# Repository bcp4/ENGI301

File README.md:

<h1>ENGI301</h1>
Repository for ENGI301

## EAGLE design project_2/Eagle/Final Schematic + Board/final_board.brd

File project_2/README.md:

This project involved creating a schematic as well as a printed circuit board for an etch a sketch. Students were tasked with importing an SPI screen in addition
to utilizing the libraries from class. Students were then able to submit their boards to macrofab.com and get an estimate for what it might cost to produce 
these PCB boards in bulk. As a result, students were able to gain a better understanding of how to create schematics and wire PCBs, as well as the process of 
documenting such a project for manufacturing and documentation reasons. 
What to expect in project_2
  -final schematic + board for the etch-a-sketch device
  -manufacturing documents (gerber files + assembly + drill files)
  -documentation (photos of top and bottom of board + mechanical drawing) 
  -bill of materials 
  -PDF of final schematic

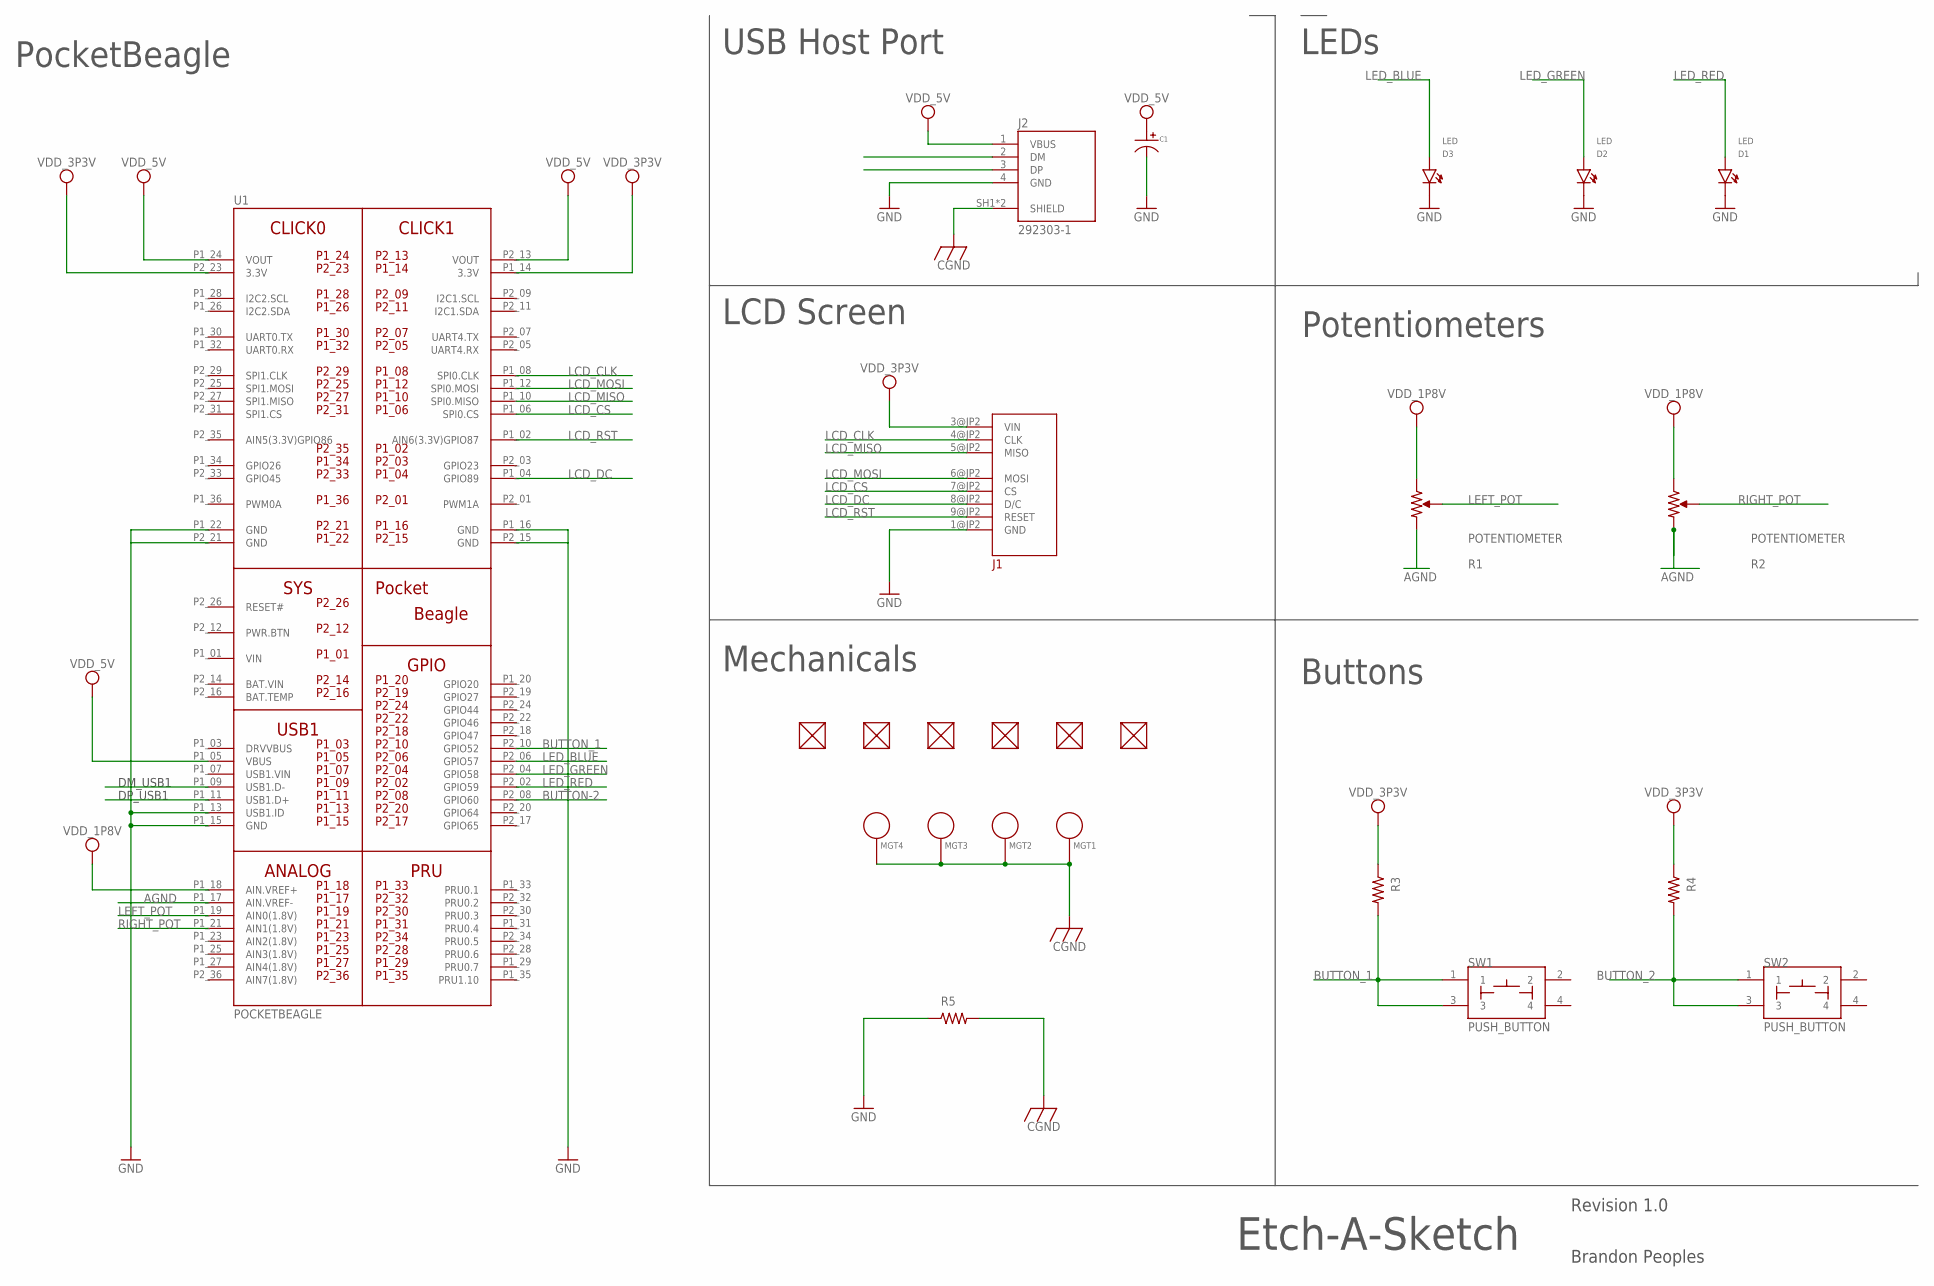
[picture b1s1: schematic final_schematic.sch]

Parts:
C1: CAPACITOR_P_10MM; CP10MM
D1, D2, D3: LED; EIA-STD
FUD1, FUD2, FUD4, FUD5, FUD6, FUD7: FIDUCIAL; FIDUCIAL_40MIL
J1: LCD; TFT_LCD_PCB
J2: 292303-1; TE_292303-1
MGT1, MGT2, MGT3, MGT4: MOUNTING_HOLE
R1, R2: POTENTIOMETER; POT-PO90S
R3, R4, R5: R_R0402; R0402
SW1, SW2: PUSH_BUTTON; BUTTON_12.5MM
U1: POCKETBEAGLE

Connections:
AGND: R1.CW, R2.CW, U1.P1_17 (AIN.VREF-)
BAT.VIN: U1.P2_14 (BAT.VIN)
BUTTON-2: U1.P2_08 (GPIO60)
BUTTON_1: R3.2, SW1.1, SW1.3, U1.P2_10 (GPIO52)
BUTTON_2: R4.2, SW2.1, SW2.3
CGND: J2.SH1 (SHIELD), J2.SH2 (SHIELD), MGT1.P$1, MGT2.P$1, MGT3.P$1, MGT4.P$1, R5.2
GND: C1.P$2, D1.CATHODE, D2.CATHODE, D3.CATHODE, J1.1@JP2 (GND), J2.4 (GND), R5.1, U1.P1_13 (USB1.ID), U1.P1_15 (GND), U1.P1_16 (GND), U1.P1_22 (GND), U1.P2_15 (GND), U1.P2_21 (GND)
LCD_CLK: J1.4@JP2 (CLK), U1.P1_08 (SPI0.CLK)
LCD_CS: J1.7@JP2 (CS), U1.P1_06 (SPI0.CS)
LCD_DC: J1.8@JP2 (D/C), U1.P1_04 (GPIO89)
LCD_MISO: J1.5@JP2 (MISO), U1.P1_10 (SPI0.MISO)
LCD_MOSI: J1.6@JP2 (MOSI), U1.P1_12 (SPI0.MOSI)
LCD_RST: J1.9@JP2 (RESET), U1.P1_02 (AIN6(3.3V)GPIO87)
LED_BLUE: D3.ANODE, U1.P2_06 (GPIO57)
LED_GREEN: D2.ANODE, U1.P2_04 (GPIO58)
LED_RED: D1.ANODE, U1.P2_02 (GPIO59)
LEFT_POT: R1.S, U1.P1_19 (AIN0(1.8V))
RIGHT_POT: R2.S, U1.P1_21 (AIN1(1.8V))
VDD_1P8V: R1.CCW, R2.CCW, U1.P1_18 (AIN.VREF+)
VDD_3P3V: J1.3@JP2 (VIN), R3.1, R4.1, U1.P1_14 (3.3V), U1.P2_23 (3.3V)
VDD_5V: C1.P$1, J2.1 (VBUS), U1.P1_05 (VBUS), U1.P1_24 (VOUT), U1.P2_13 (VOUT)
VIN: U1.P1_01 (VIN)

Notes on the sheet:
LEDs
Potentiometers
Buttons
USB Host Port
Etch-A-Sketch
LCD Screen
DM_USB1
DP_USB1
PocketBeagle
Mechanicals
Brandon Peoples
Revision 1.0

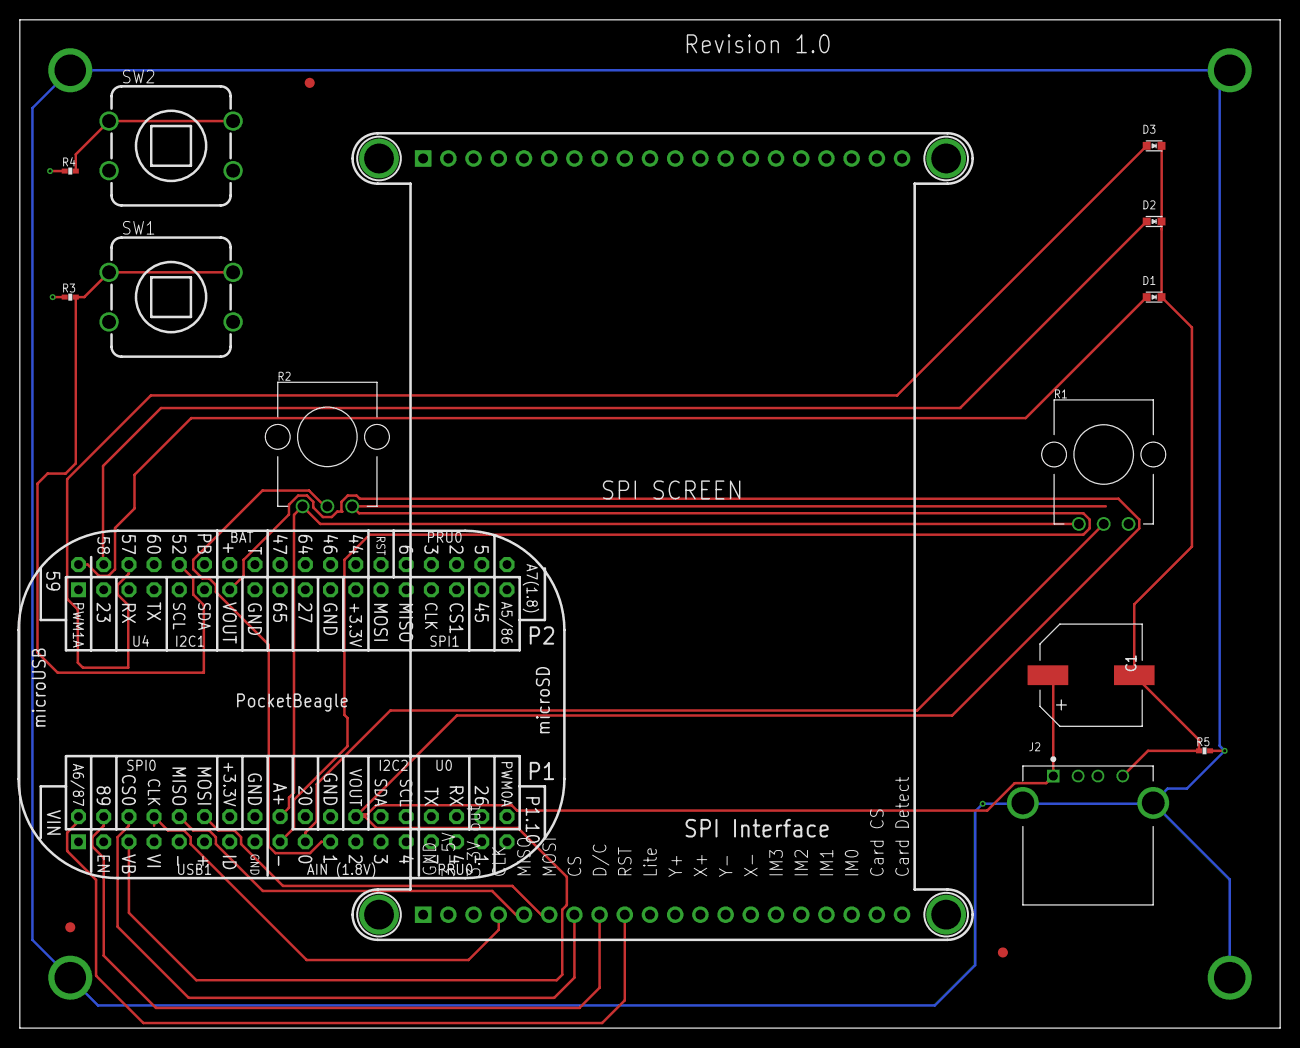
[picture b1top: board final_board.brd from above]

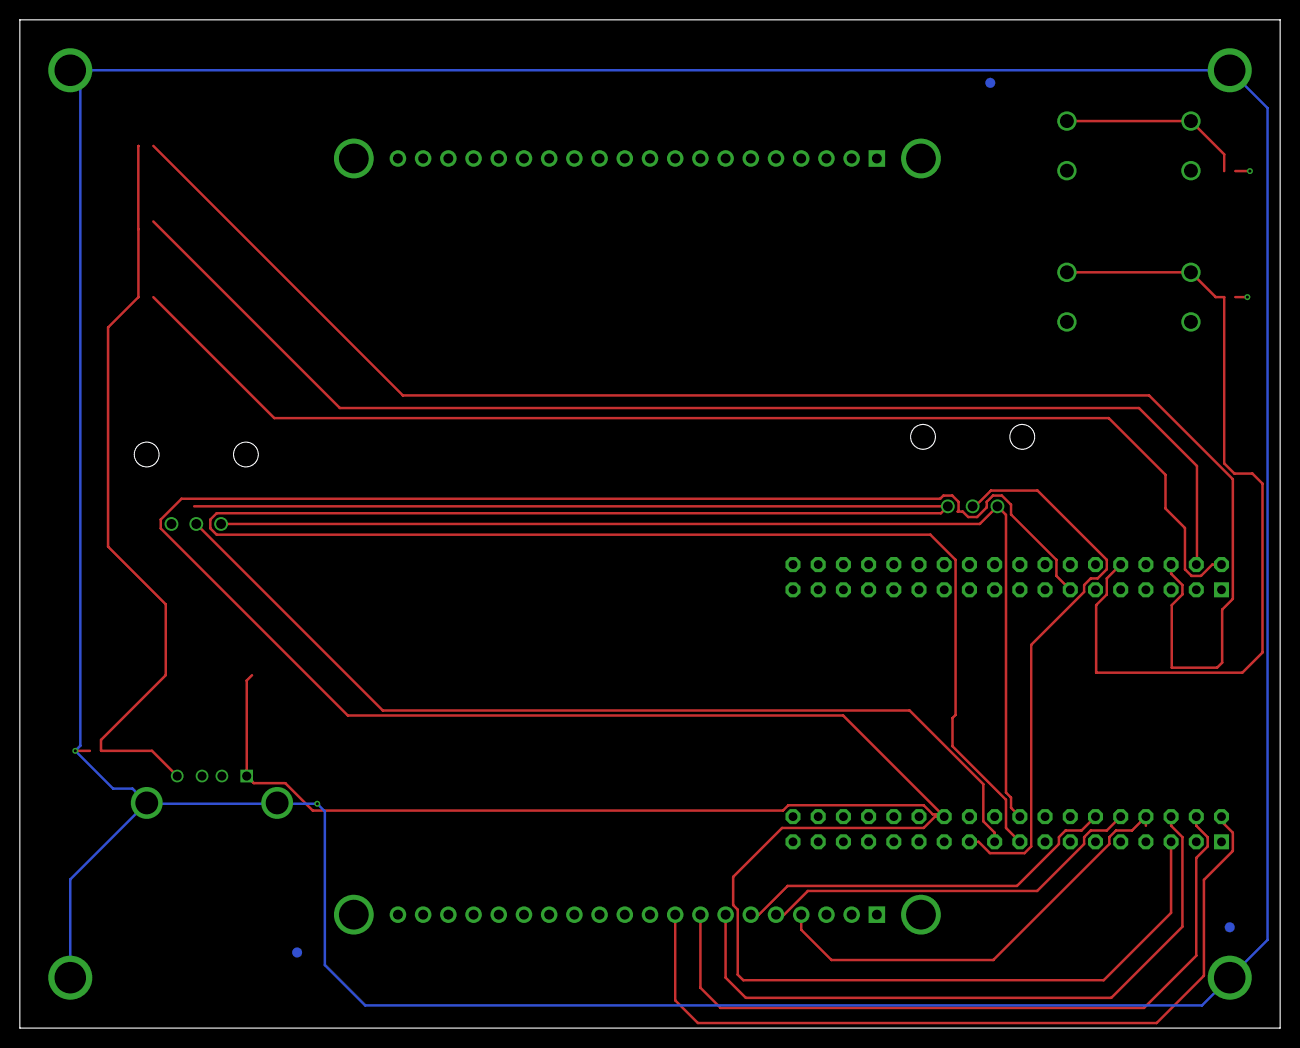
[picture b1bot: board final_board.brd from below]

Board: 4 copper layers, 127.0 x 101.6 mm, 24 parts (3 on the bottom side), 19 nets.

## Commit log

2022-09-10 Updating README.md
2022-09-24 commiting simple calc class
2022-09-24 commiting question 2 HW4
2022-10-28 Create Peoples_ENGI301_project_01_proposal.pptx
    Project Proposal Upload
2022-12-03 Adding Opener Files
    adding cloud9 code to repository
2022-12-03 Uploading project1 code
    cloud9 backup
2022-12-03 Mechanical Block Diagram
    pushing part 1 of project
2022-12-12 Project2 Upload
    Uploading Project 2 for Engi 301
2022-12-12 Project 1
    Project 1 upload
2022-12-12 Update README.md
    updated readme.med
2022-12-13 Submitting Project 1
    Final Project 1 upload
